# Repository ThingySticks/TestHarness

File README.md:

ThingySticks Test Harness
=========================

Particle Electron based test harness to test Photon based ThingyStick sticks.
Most pins of the Photon are taken to the Electron's matching pin (except VIn,  VBatt and RST).
e.g. D7 on Photon board Pogo Pins will connect to D7 on the Electron.

Board Under Test location is intended to be populated with Pogo pins or another connector system to match up with the Board Under Tests photon pads/socket.

Board under Test should not have a photon fitted.

Electron Pinout: https://docs.particle.io/assets/images/electron/illustrations/electron_pinout.pdf

Improvements for V2.1
---------------------

* 10k Pull down resistors for Q1 and Q2 relay drive FETs to prevent them oscilating when not connected.
* Add a button to start the test (e.g. Use C4).
* Add high side current monitor so PCB can be tested for shorts.
* Make use of I2C(2) on the Electrons C4/C5 pins (needs VIn relay to be driven from a different pin - maybe C0 - with a jumper so it can be disabled).
** Use full for current monitor
* B5,4 or 3 to measure voltage at VIn so that the USB power connection can be simulated (low priority).
* Diode on VIn from Electron so we don't try and power the relays and back feed the 5V regulator when running on USB or battery only.

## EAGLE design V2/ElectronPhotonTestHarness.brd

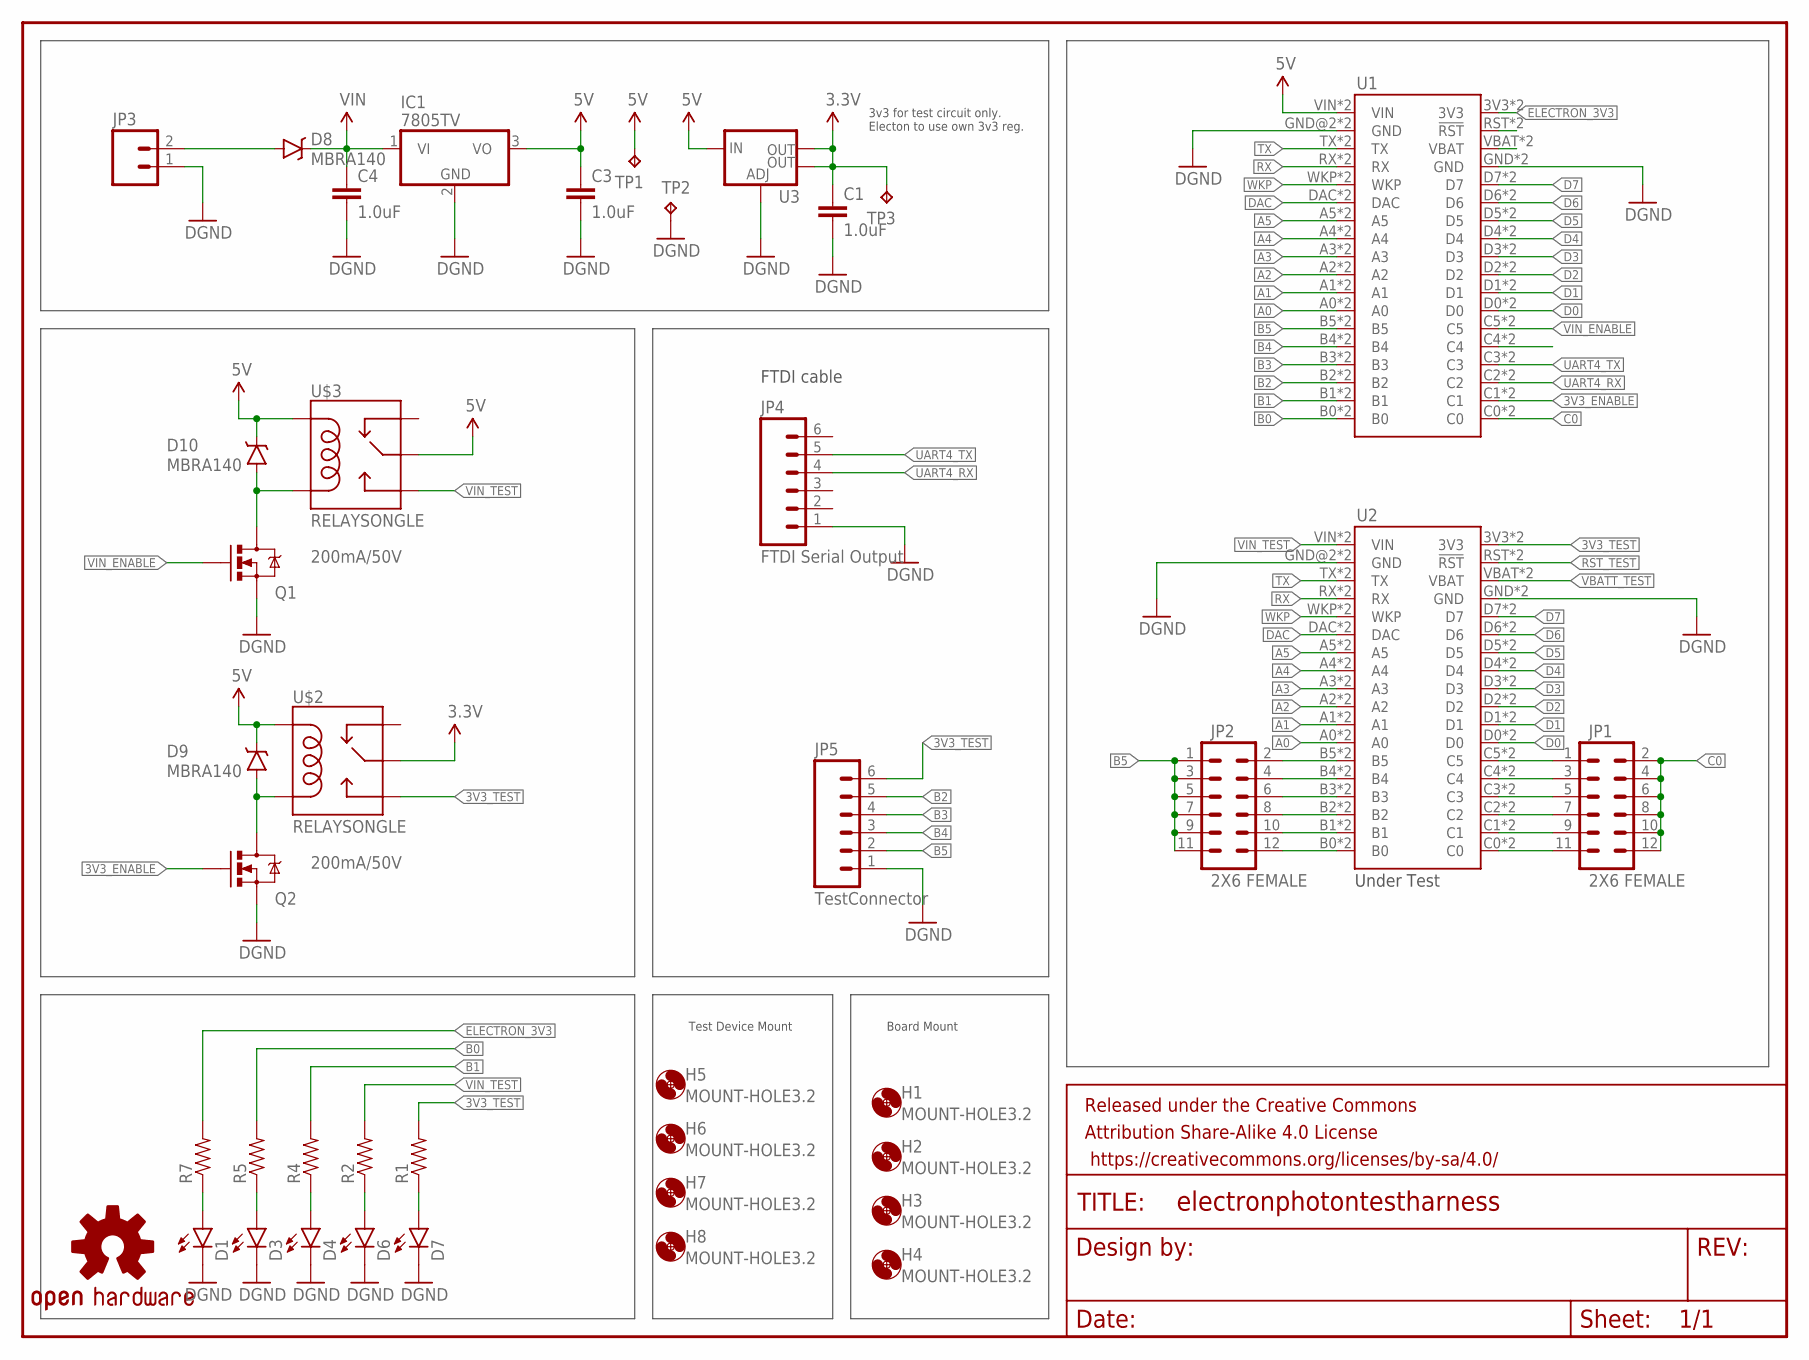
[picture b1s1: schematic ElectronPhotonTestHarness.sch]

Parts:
C1, C3, C4: 1.0uF; 0805-CAP
D1: LED1206-BOTTOM; LED-1206-BOTTOM
D3, D4, D6, D7: LED1206; LED-1206
D8, D9, D10: MBRA140; SMA-DIODE
FRAME1: FRAME-LETTER; CREATIVE_COMMONS
H1, H2, H3, H4, H5, H6, H7, H8: MOUNT-HOLE3.2; 3,2
IC1: 7805TV; TO220V
JP1, JP2: 2X6 FEMALE; 2X6
JP3: M025MM; SCREWTERMINAL-5MM-2
JP4: FTDI Serial Output; 1X06
JP5: TestConnector; 1X06
LOGO1: OSHW-LOGOL; OSHW-LOGO-L
Q1, Q2: 200mA/50V; SOT23-3
R1, R2, R4, R5, R7: RESISTOR1206; 1206
TP1, TP2, TP3: TPTP12SQ; TP12SQ
U1: ELECTRONDUALNAMED; ELECTRON_SIMPLE_SILK_NAMES_DUAL
U2: UnderTest; ELECTRON_SIMPLE_SILK_NAMES_DUAL
U3: V_REG_LM1117SOT223; SOT223
U$2, U$3: RELAYSONGLE; SRD-5VDC-SL-C

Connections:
3.3V: C1.1, TP3.TP, U3.2 (OUT), U3.4 (OUT), U$2.COMMON (MAIN)
3V3_ENABLE: Q2.1 (G), U1.C1, U1.C1_1 (C1)
3V3_TEST: JP5.6, R1.2, U2.3V3, U2.3V3_1 (3V3), U$2.OPEN (NO)
5V: C3.1, D9.C, D10.C, IC1.3 (VO), TP1.TP, U1.VIN, U1.VIN_1B (VIN), U3.3 (IN), U$2.COIL1, U$3.COIL1, U$3.COMMON (MAIN)
A0: U1.A0, U1.A0_1 (A0), U2.A0, U2.A0_1 (A0)
A1: U1.A1, U1.A1_1 (A1), U2.A1, U2.A1_1 (A1)
A2: U1.A2, U1.A2_1 (A2), U2.A2, U2.A2_1 (A2)
A3: U1.A3, U1.A3_1 (A3), U2.A3, U2.A3_1 (A3)
A4: U1.A4, U1.A4_1 (A4), U2.A4, U2.A4_1 (A4)
A5: U1.A5, U1.A5_1 (A5), U2.A5, U2.A5_1 (A5)
B0: R5.2, U1.B0, U1.B0_1 (B0)
B1: R4.2, U1.B1, U1.B1_1 (B1)
B2: JP5.5, U1.B2, U1.B2_1 (B2)
B3: JP5.4, U1.B3, U1.B3_1 (B3)
B4: JP5.3, U1.B4, U1.B4_1 (B4)
B5: JP2.1, JP2.3, JP2.5, JP2.7, JP2.9, JP2.11, JP5.2, U1.B5, U1.B5_1 (B5)
C0: JP1.2, JP1.4, JP1.6, JP1.8, JP1.10, JP1.12, U1.C0, U1.C0_1 (C0)
D0: U1.D0, U1.D0_1 (D0), U2.D0, U2.D0_1 (D0)
D1: U1.D1, U1.D1_1 (D1), U2.D1, U2.D1_1 (D1)
D2: U1.D2, U1.D2_1 (D2), U2.D2, U2.D2_1 (D2)
D3: U1.D3, U1.D3_1 (D3), U2.D3, U2.D3_1 (D3)
D4: U1.D4, U1.D4_1 (D4), U2.D4, U2.D4_1 (D4)
D5: U1.D5, U1.D5_1 (D5), U2.D5, U2.D5_1 (D5)
D6: U1.D6, U1.D6_1 (D6), U2.D6, U2.D6_1 (D6)
D7: U1.D7, U1.D7_1 (D7), U2.D7, U2.D7_1 (D7)
DAC: U1.DAC, U1.DAC_1 (DAC), U2.DAC, U2.DAC_1 (DAC)
ELECTRON_3V3: R7.2, U1.3V3, U1.3V3_1 (3V3)
GND: C1.2, C3.2, C4.2, D1.C, D3.C, D4.C, D6.C, D7.C, IC1.2 (GND), JP3.1, JP4.1, JP5.1, Q1.2 (S), Q2.2 (S), TP2.TP, U1.GND, U1.GND@2 (GND), U1.GND_1 (GND), U1.GND_1B (GND), U2.GND, U2.GND@2 (GND), U2.GND_1 (GND), U2.GND_1B (GND), U3.1 (ADJ)
unnamed: JP2.2, U2.B5, U2.B5_1 (B5)
unnamed: JP2.4, U2.B4, U2.B4_1 (B4)
unnamed: JP2.6, U2.B3, U2.B3_1 (B3)
unnamed: JP2.8, U2.B2, U2.B2_1 (B2)
unnamed: JP2.10, U2.B1, U2.B1_1 (B1)
unnamed: JP2.12, U2.B0, U2.B0_1 (B0)
unnamed: JP1.11, U2.C0, U2.C0_1 (C0)
unnamed: JP1.9, U2.C1, U2.C1_1 (C1)
unnamed: JP1.7, U2.C2, U2.C2_1 (C2)
unnamed: JP1.5, U2.C3, U2.C3_1 (C3)
unnamed: JP1.3, U2.C4, U2.C4_1 (C4)
unnamed: JP1.1, U2.C5, U2.C5_1 (C5)
unnamed: D1.A, R7.1
unnamed: U1.RST (!RST), U1.RST_1 (!RST)
unnamed: D3.A, R5.1
unnamed: D4.A, R4.1
unnamed: U1.VBAT, U1.VBATT_1 (VBAT)
unnamed: D6.A, R2.1
unnamed: D7.A, R1.1
unnamed: D8.A, JP3.2
unnamed: U1.C4, U1.C4_1 (C4)
RELAY_3V3: D9.A, Q2.3 (D), U$2.COIL2
RELAY_5V: D10.A, Q1.3 (D), U$3.COIL2
RST_TEST: U2.RST (!RST), U2.RST_1 (!RST)
RX: U1.RX, U1.RX_1 (RX), U2.RX, U2.RX_1 (RX)
TX: U1.TX, U1.TX_1 (TX), U2.TX, U2.TX_1 (TX)
UART4_RX: JP4.4, U1.C2, U1.C2_1 (C2)
UART4_TX: JP4.5, U1.C3, U1.C3_1 (C3)
VBATT_TEST: U2.VBAT, U2.VBATT_1 (VBAT)
VIN: C4.1, D8.C, IC1.1 (VI)
VIN_ENABLE: Q1.1 (G), U1.C5, U1.C5_1 (C5)
VIN_TEST: R2.2, U2.VIN, U2.VIN_1B (VIN), U$3.OPEN (NO)
WKP: U1.WKP, U1.WKP_1 (WKP), U2.WKP, U2.WKP_1 (WKP)

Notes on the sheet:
Under Test
3v3 for test circuit only. Electon to use own 3v3 reg.
FTDI cable
Test Device Mount
Board Mount

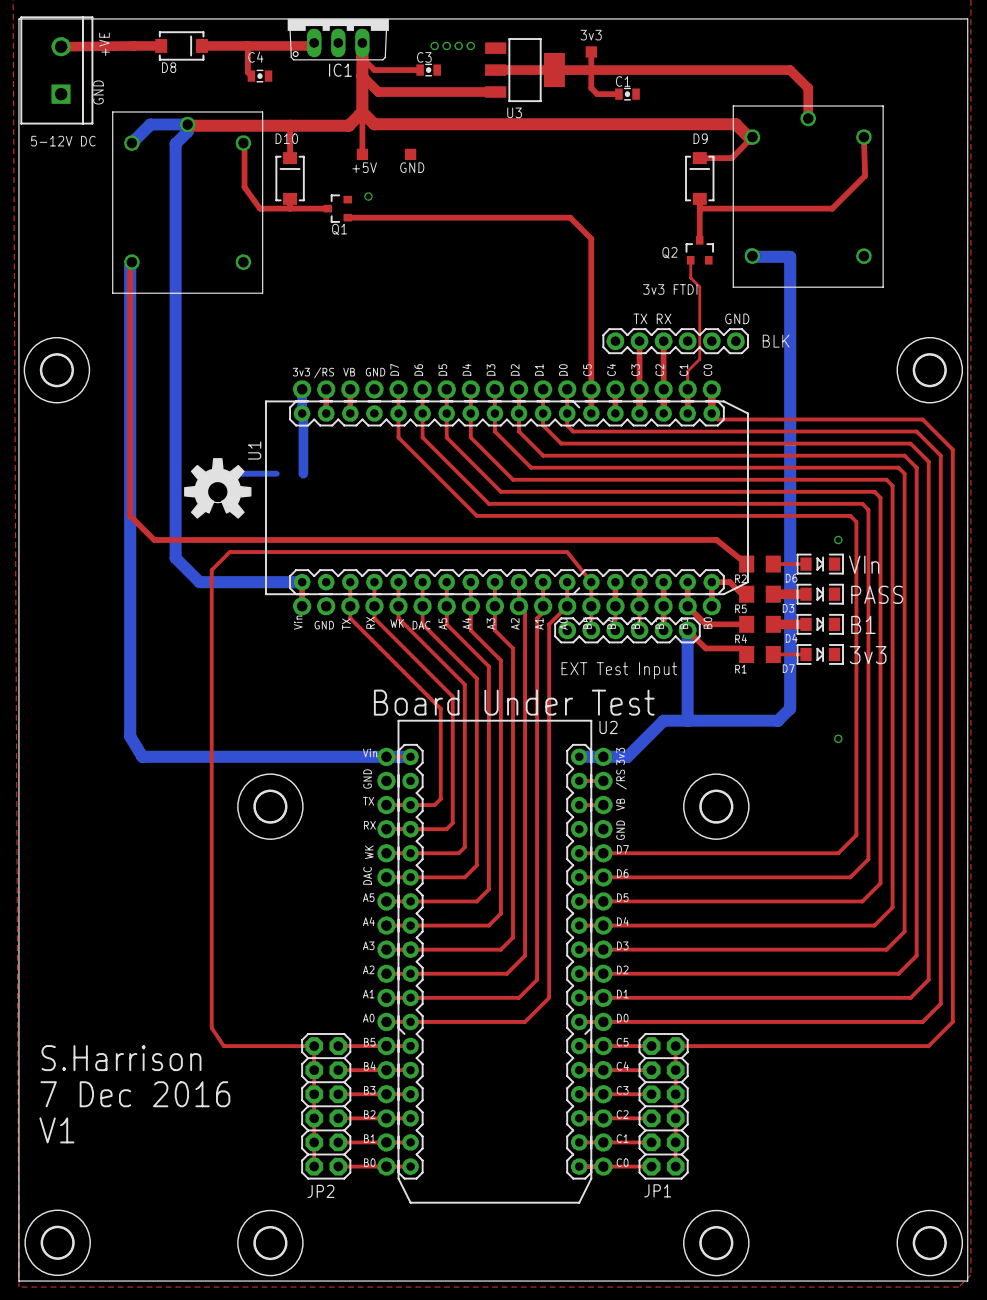
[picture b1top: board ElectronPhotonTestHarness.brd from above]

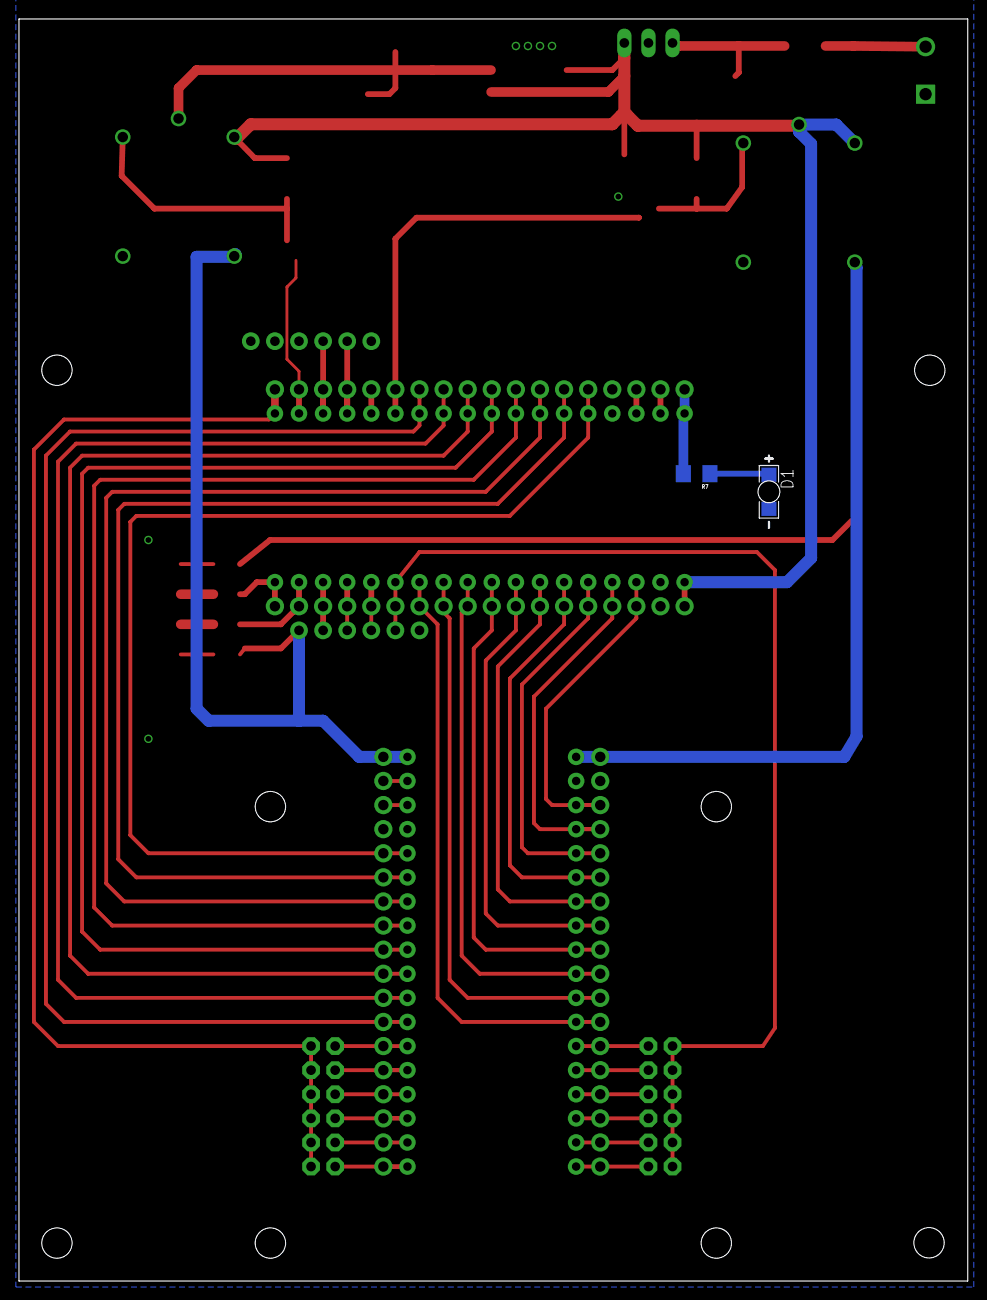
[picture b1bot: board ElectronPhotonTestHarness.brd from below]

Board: 2 copper layers, 100.0 x 133.0 mm, 42 parts (2 on the bottom side), 61 nets.

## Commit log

2016-12-07 Initial version of test board using Electron to run tests for a photon with additional outputs.
2016-12-07 Added ,gitignore
2016-12-07 Tidy up for main test harness board.
    Made test top (well middle) board for Pogo pins to rest in.
2016-12-07 Added name and version (post sending to DirtyPCBs)
2016-12-07 Added PCB images as generated by DirtyPCBs
2016-12-07 Added pdfs
2016-12-20 Added jig for thermocouple PCB.
2016-12-20 Initial implementation for Thermocouple test
2016-12-22 Improved sizings for the Thermocouple holder jig.
2017-08-07 Improved PCB holders.
2017-08-07 Refacored a little to take common calculations out of methods.
    Changed USB cutout option to go all the way to the PCB pin (i.e. as far as possible)
    Added text inset to identify the blocks.
2017-08-08 Added build.bat to make all the stl's
    Split out each pcb to it's own scad file
2017-08-08 Added base for test jig.
2017-08-08 Rebuild pcb holders for test jig
2017-08-12 Improved board feet.
2017-08-12 Added jigs for current monitor, latching relay and quad p-fets
    tweaked height that the PCB sits at for a better pogo pin contact.
    made pcb cutout in the base part deeper so the PCB can sit flush with the top of the base, and hence the push down tool sit flush with the base section.

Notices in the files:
parts and their libraries:
SparkFun-LED: Licensing: Creative Commons ShareAlike 4.0 International - https://creativecommons.org/licenses/by-sa/4.0
SparkFun-Aesthetics: Released under the Creative Commons Attribution Share-Alike 4.0 License
SparkFun-Aesthetics: https://creativecommons.org/licenses/by-sa/4.0
